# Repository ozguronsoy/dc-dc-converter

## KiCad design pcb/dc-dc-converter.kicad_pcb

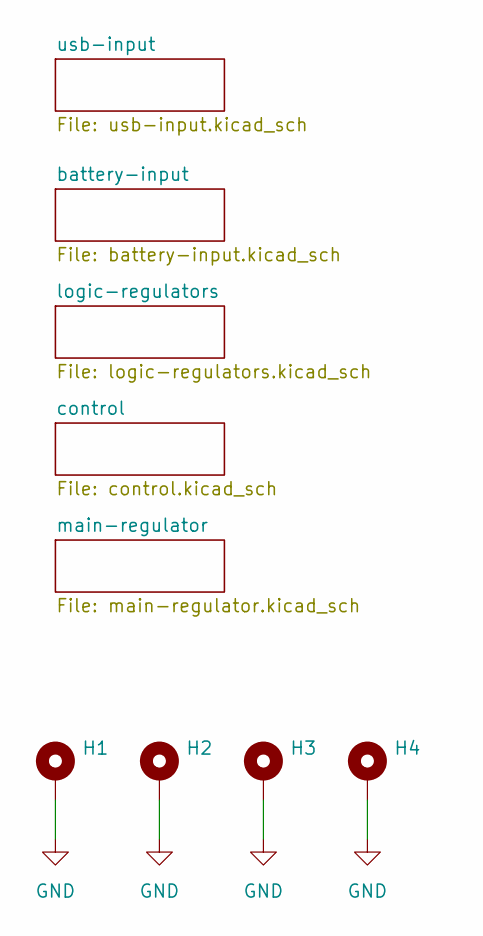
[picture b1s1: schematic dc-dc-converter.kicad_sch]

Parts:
H1, H2, H3, H4: MountingHole_Pad; MountingHole_4.3mm_M4_Pad

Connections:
GND: H1.1, H2.1, H3.1, H4.1; also elsewhere on the board

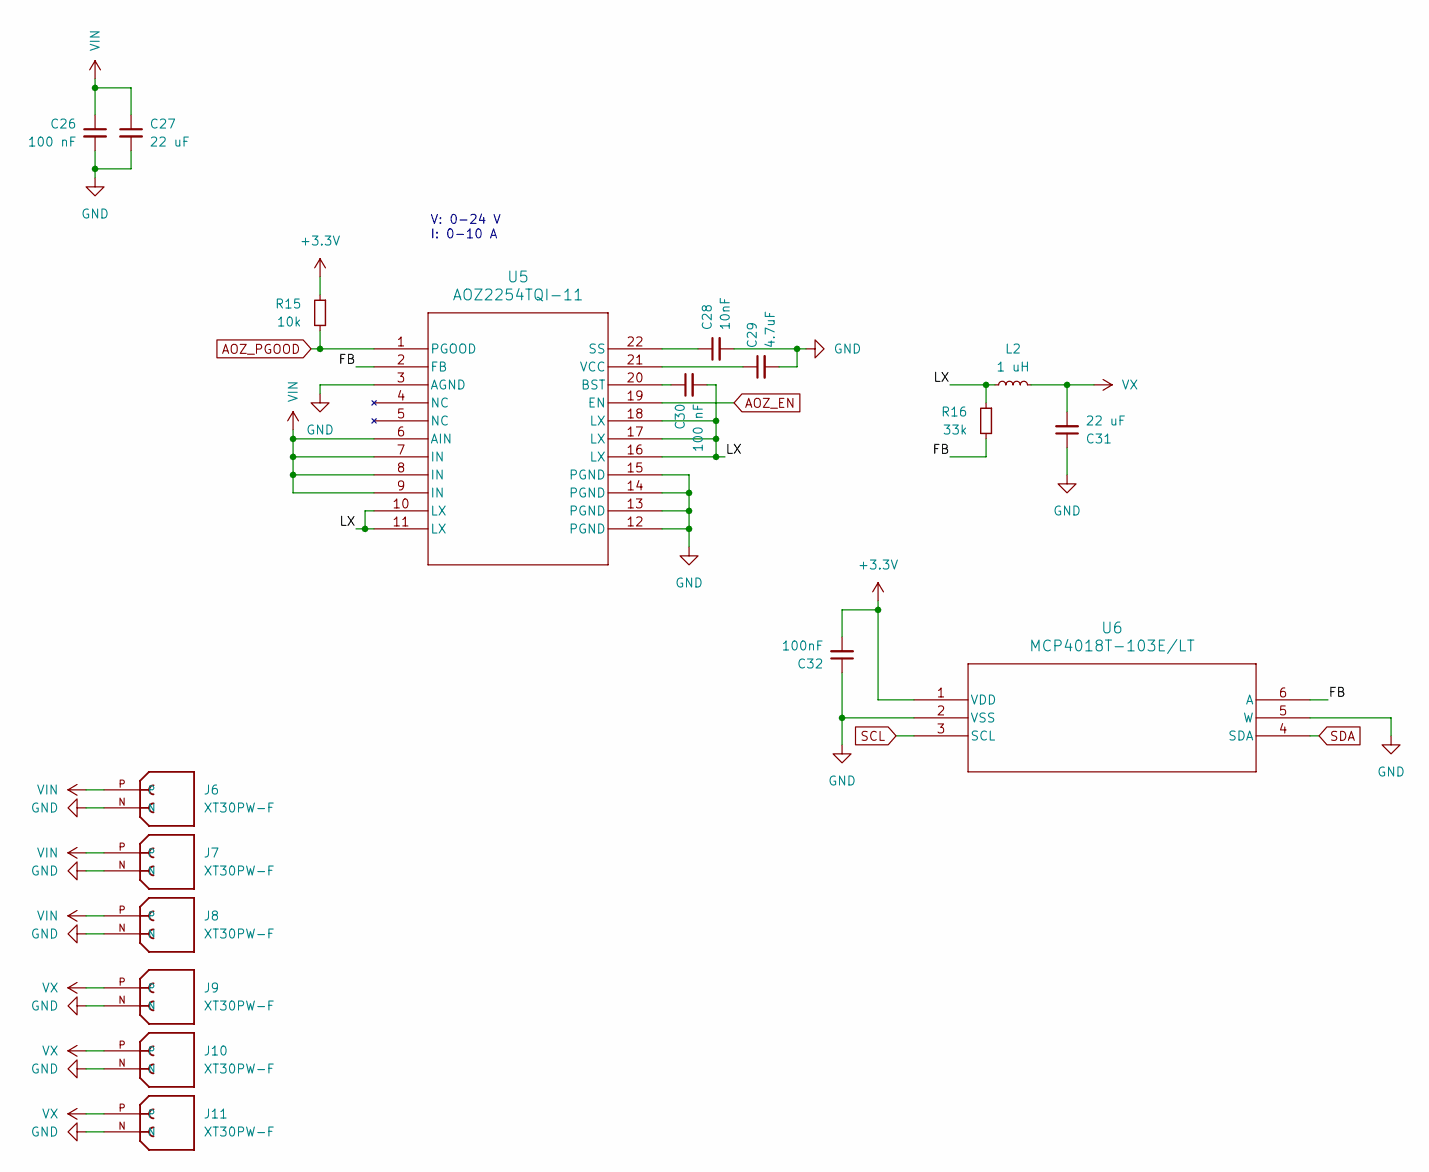
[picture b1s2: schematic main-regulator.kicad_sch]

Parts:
C26: 100 nF; C_0805_2012Metric
C27, C31: 22 uF; C_0805_2012Metric
C28: 10nF; C_0603_1608Metric
C29: 4.7uF; C_0603_1608Metric
C30: 100 nF; C_0603_1608Metric
C32: 100nF; C_0603_1608Metric
J6, J7, J8, J9, J10, J11: XT30PW-F; PARTREV 1.2
L2: 1 uH; L_Chilisin_BMRB00060624
R15: 10k; R_0603_1608Metric
R16: 33k; R_0603_1608Metric
U5: AOZ2254TQI-11
U6: MCP4018T-103E/LT; MCP4018T

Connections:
+3.3V: C32.2, R15.1, U6.1 (VDD); also elsewhere on the board
/main-regulator/FB: R16.2, U5.2 (FB), U6.6 (A)
/main-regulator/LX: C30.2, L2.1, R16.1, U5.10 (LX), U5.11 (LX), U5.16 (LX), U5.17 (LX), U5.18 (LX)
AOZ_EN: U5.19 (EN); also elsewhere on the board
AOZ_PGOOD: R15.2, U5.1 (PGOOD); also elsewhere on the board
GND: C26.2, C27.2, C28.2, C29.2, C31.1, C32.1, J6.N, J7.N, J8.N, J9.N, J10.N, J11.N, U5.3 (AGND), U5.12 (PGND), U5.13 (PGND), U5.14 (PGND), U5.15 (PGND), U6.2 (VSS), U6.5 (W); also elsewhere on the board
unnamed: C30.1, U5.20 (BST)
unnamed: C28.1, U5.22 (SS)
unnamed: C29.1, U5.21 (VCC)
SCL: U6.3 (SCL); also elsewhere on the board
SDA: U6.4 (SDA); also elsewhere on the board
VIN: C26.1, C27.1, J6.P, J7.P, J8.P, U5.6 (AIN), U5.7 (IN), U5.8 (IN), U5.9 (IN); also elsewhere on the board
VX: C31.2, J9.P, J10.P, J11.P, L2.2; also elsewhere on the board

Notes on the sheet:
V: 0-24 V I: 0-10 A

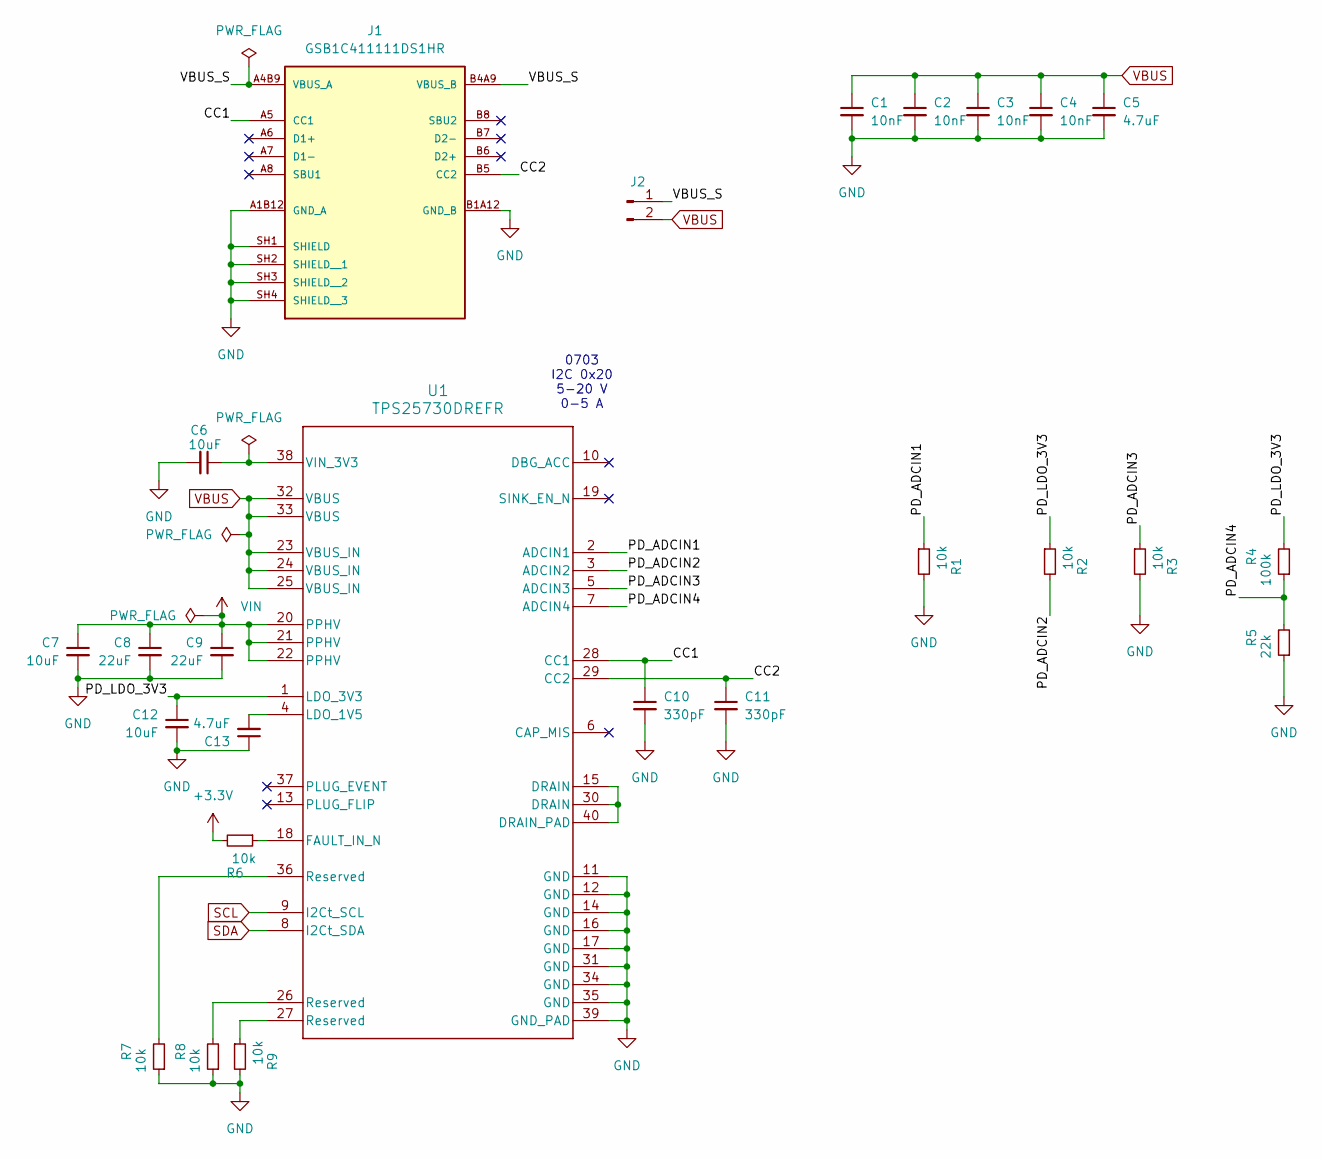
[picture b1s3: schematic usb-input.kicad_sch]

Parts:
C1, C2, C3, C4: 10nF; C_0603_1608Metric
C5, C13: 4.7uF; C_0603_1608Metric
C6, C12: 10uF; C_0603_1608Metric
C7: 10uF; C_0805_2012Metric
C8, C9: 22uF; C_0805_2012Metric
C10, C11: 330pF; C_0402_1005Metric
J1: GSB1C411111DS1HR; PARTREV AX3
J2: Conn_01x02_Pin; PinHeader_1x02_P2.54mm_Vertical
R1, R2, R3, R6, R7, R8, R9: 10k; R_0603_1608Metric
R4: 100k; R_0603_1608Metric
R5: 22k; R_0603_1608Metric
U1: TPS25730DREFR

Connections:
+3.3V: R6.2; also elsewhere on the board
/usb-input/CC1: C10.1, J1.A5 (CC1), U1.28 (CC1)
/usb-input/CC2: C11.1, J1.B5 (CC2), U1.29 (CC2)
/usb-input/PD_ADCIN1: R1.1, U1.2 (ADCIN1)
/usb-input/PD_ADCIN2: R2.2, U1.3 (ADCIN2)
/usb-input/PD_ADCIN3: R3.1, U1.5 (ADCIN3)
/usb-input/PD_ADCIN4: R4.1, R5.2, U1.7 (ADCIN4)
/usb-input/PD_LDO_3V3: C12.1, R2.1, R4.2, U1.1 (LDO_3V3)
/usb-input/VBUS_S: J1.A4B9 (VBUS_A), J1.B4A9 (VBUS_B), J2.1; also elsewhere on the board
GND: C1.2, C2.2, C3.2, C4.2, C5.2, C6.2, C7.2, C8.2, C9.2, C10.2, C11.2, C12.2, C13.1, J1.A1B12 (GND_A), J1.B1A12 (GND_B), J1.SH1 (SHIELD), J1.SH2 (SHIELD__1), J1.SH3 (SHIELD__2), J1.SH4 (SHIELD__3), R1.2, R3.2, R5.1, R7.1, R8.1, R9.2, U1.11 (GND), U1.12 (GND), U1.14 (GND), U1.16 (GND), U1.17 (GND), U1.31 (GND), U1.34 (GND), U1.35 (GND), U1.39 (GND_PAD), U1.44, U1.45, U1.46, U1.47, U1.48; also elsewhere on the board
unnamed: R7.2, U1.36 (Reserved)
unnamed: R8.2, U1.26 (Reserved)
unnamed: R9.1, U1.27 (Reserved)
unnamed: U1.15 (DRAIN), U1.30 (DRAIN), U1.40 (DRAIN_PAD)
unnamed: R6.1, U1.18 (FAULT_IN_N)
unnamed: C13.2, U1.4 (LDO_1V5)
unnamed: C6.1, U1.38 (VIN_3V3)
SCL: U1.9 (I2Ct_SCL); also elsewhere on the board
SDA: U1.8 (I2Ct_SDA); also elsewhere on the board
VBUS: C1.1, C2.1, C3.1, C4.1, C5.1, J2.2, U1.23 (VBUS_IN), U1.24 (VBUS_IN), U1.25 (VBUS_IN), U1.32 (VBUS), U1.33 (VBUS); also elsewhere on the board
VIN: C7.1, C8.1, C9.1, U1.20 (PPHV), U1.21 (PPHV), U1.22 (PPHV); also elsewhere on the board

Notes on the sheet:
0703 I2C 0x20 5-20 V 0-5 A

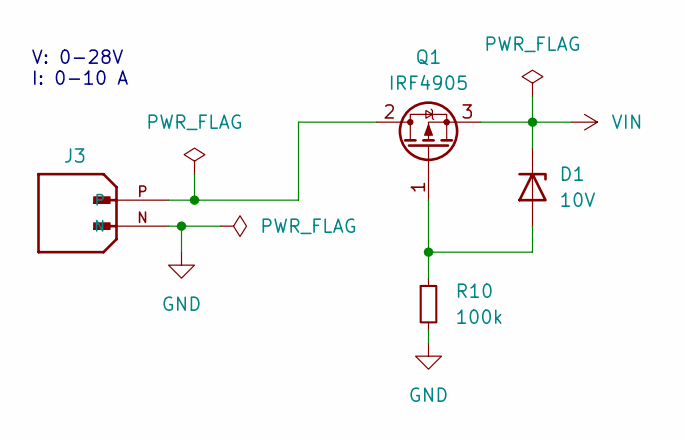
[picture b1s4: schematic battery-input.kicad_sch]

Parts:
D1: 10V; D_SOD-523
J3: XT30PW-M; PARTREV 1.2
Q1: IRF4905; TO-220-3_Vertical
R10: 100k; R_0603_1608Metric

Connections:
GND: J3.N, R10.2; also elsewhere on the board
unnamed: D1.2 (A), Q1.1 (G), R10.1
unnamed: J3.P, Q1.2 (D)
VIN: D1.1 (K), Q1.3 (S); also elsewhere on the board

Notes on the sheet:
V: 0-28V I: 0-10 A

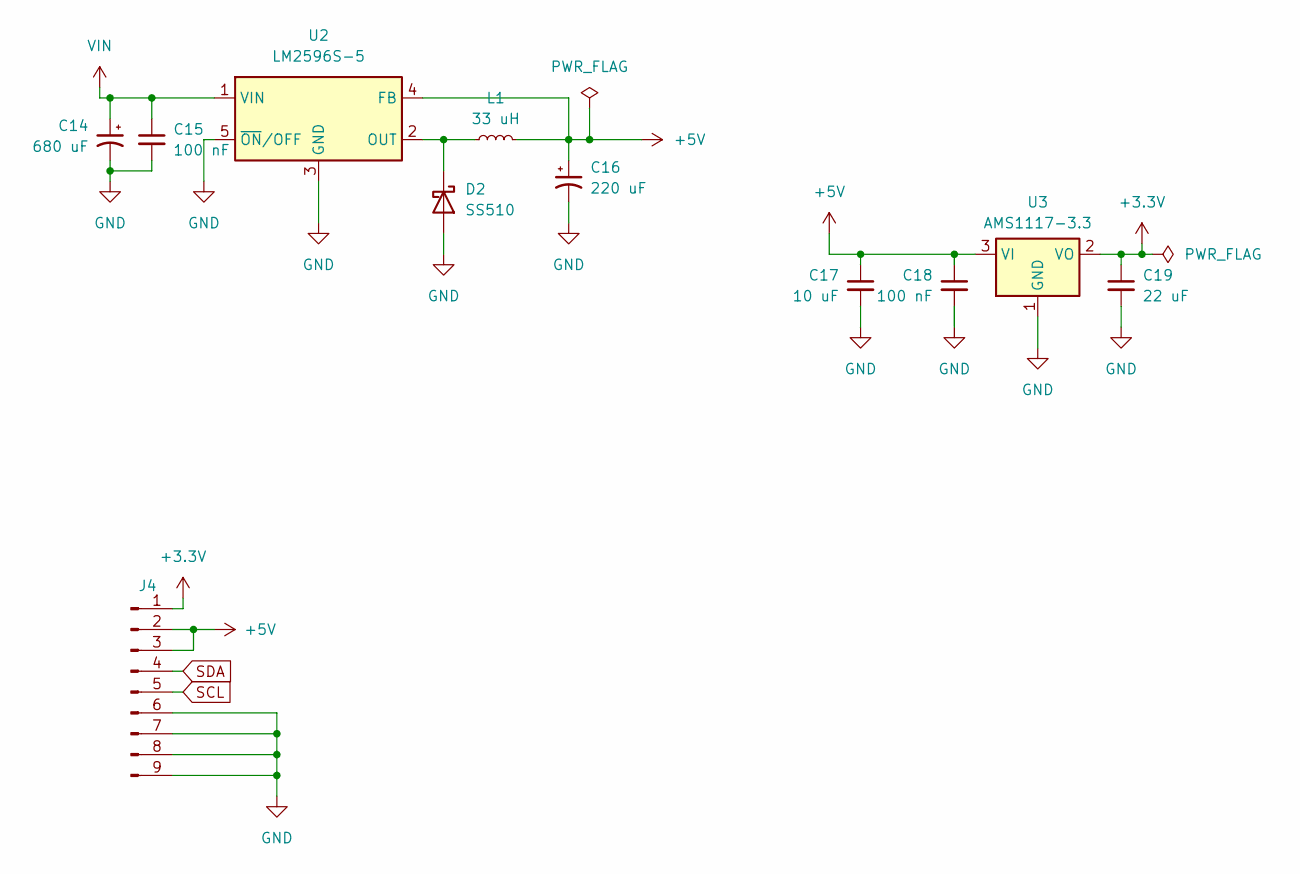
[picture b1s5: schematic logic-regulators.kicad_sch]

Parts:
C14: 680 uF; C_Radial_D12.5mm_H20.0mm_P5.00mm
C15: 100 nF; C_0805_2012Metric
C16: 220 uF; C_Radial_D12.5mm_H20.0mm_P5.00mm
C17: 10 uF; C_0603_1608Metric
C18: 100 nF; C_0603_1608Metric
C19: 22 uF; C_0603_1608Metric
D2: SS510; D_SMA
J4: JST_EH_B9B-EH-A_1x09_P2.50mm_Vertical
L1: 33 uH; L_SXN_SMDRI127
U2: LM2596S-5; TO-263-5_TabPin3
U3: AMS1117-3.3; SOT-223-3_TabPin2

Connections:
+3.3V: C19.1, J4.1, U3.2 (VO); also elsewhere on the board
+5V: C16.1, C17.1, C18.1, J4.2, J4.3, L1.2, U2.4 (FB), U3.3 (VI); also elsewhere on the board
GND: C14.2, C15.2, C16.2, C17.2, C18.2, C19.2, D2.2 (A), J4.6, J4.7, J4.8, J4.9, U2.3 (GND), U2.5 (~ON/OFF), U3.1 (GND); also elsewhere on the board
unnamed: D2.1 (K), L1.1, U2.2 (OUT)
SCL: J4.5; also elsewhere on the board
SDA: J4.4; also elsewhere on the board
VIN: C14.1, C15.1, U2.1 (VIN); also elsewhere on the board

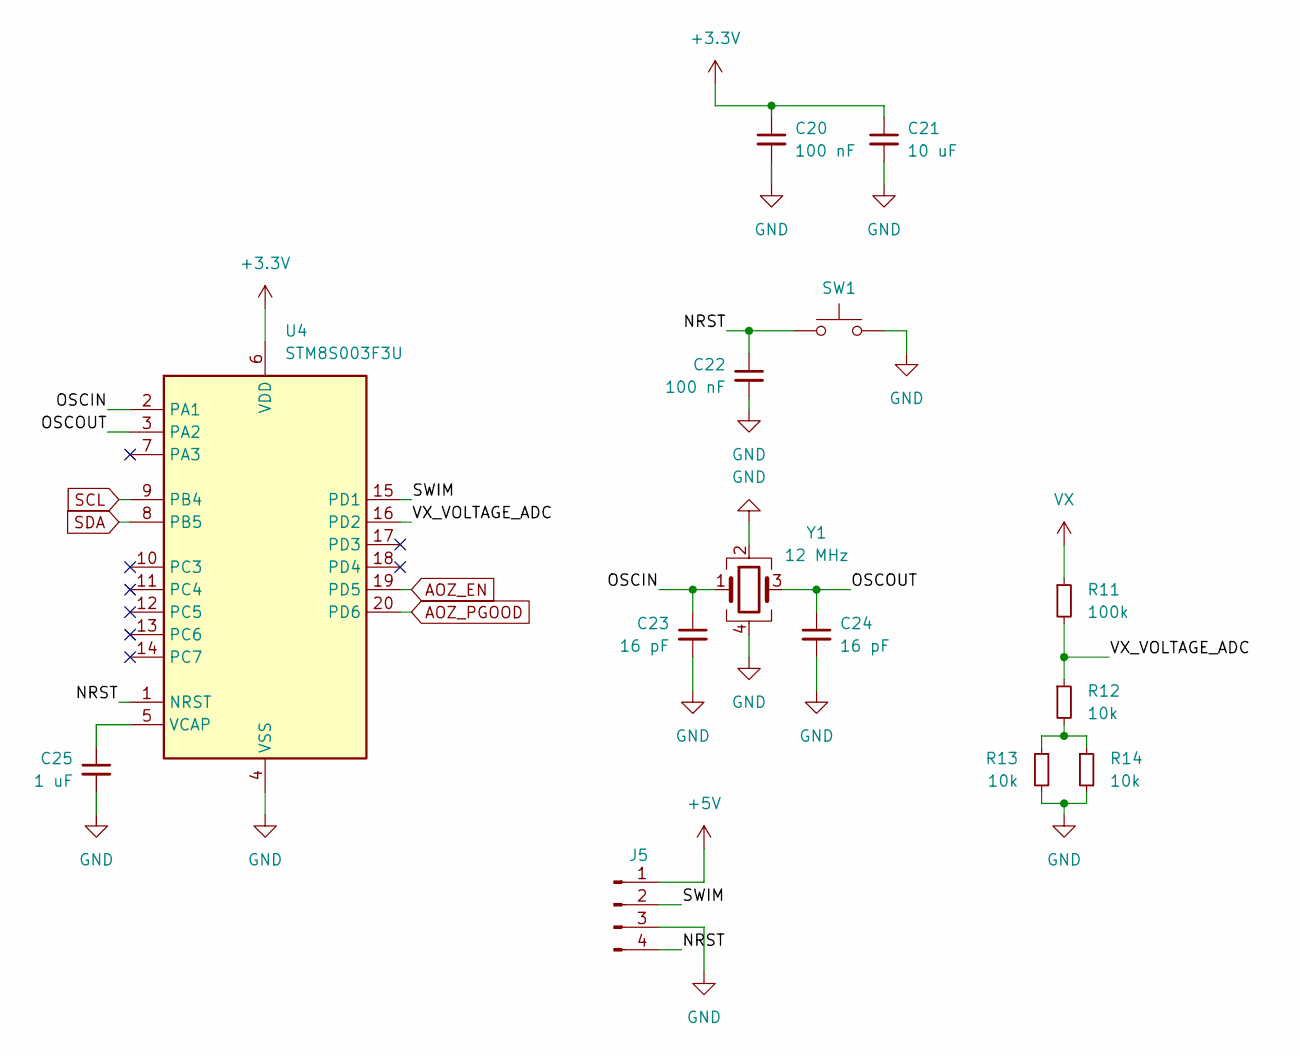
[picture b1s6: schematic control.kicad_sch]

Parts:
C20, C22: 100 nF; C_0603_1608Metric
C21: 10 uF; C_0603_1608Metric
C23, C24: 16 pF; C_0402_1005Metric
C25: 1 uF; C_0603_1608Metric
J5: Conn_01x04_Pin; PinHeader_1x04_P2.54mm_Vertical
R11: 100k; R_0603_1608Metric
R12, R13, R14: 10k; R_0603_1608Metric
SW1: SW_Push; SW_Tactile_SPST_NO_Straight_CK_PTS636Sx25SMTRLFS
U4: STM8S003F3U; ST_UFQFPN-20_3x3mm_P0.5mm
Y1: 12 MHz; Crystal_SMD_3225-4Pin_3.2x2.5mm

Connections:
+3.3V: C20.1, C21.1, U4.6 (VDD); also elsewhere on the board
+5V: J5.1; also elsewhere on the board
/control/NRST: C22.1, J5.4, SW1.1, U4.1 (NRST)
/control/OSCIN: C23.1, U4.2 (PA1), Y1.1
/control/OSCOUT: C24.1, U4.3 (PA2), Y1.3
/control/SWIM: J5.2, U4.15 (PD1)
/control/VX_VOLTAGE_ADC: R11.2, R12.1, U4.16 (PD2)
AOZ_EN: U4.19 (PD5); also elsewhere on the board
AOZ_PGOOD: U4.20 (PD6); also elsewhere on the board
GND: C20.2, C21.2, C22.2, C23.2, C24.2, C25.2, J5.3, R13.2, R14.2, SW1.2, U4.4 (VSS), Y1.2, Y1.4; also elsewhere on the board
unnamed: R12.2, R13.1, R14.1
unnamed: C25.1, U4.5 (VCAP)
SCL: U4.9 (PB4); also elsewhere on the board
SDA: U4.8 (PB5); also elsewhere on the board
VX: R11.1; also elsewhere on the board

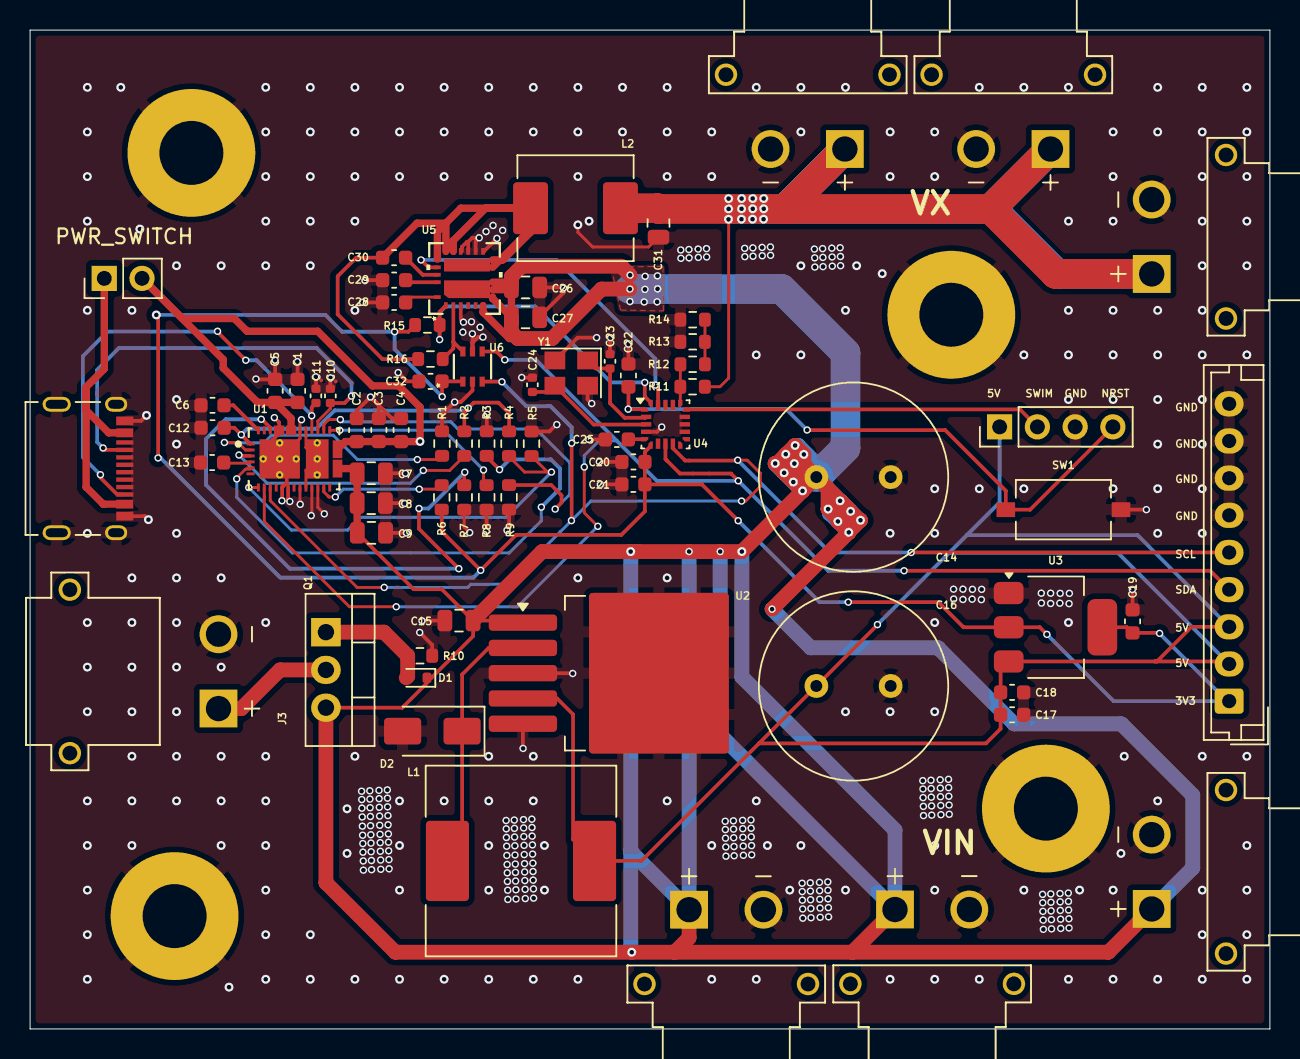
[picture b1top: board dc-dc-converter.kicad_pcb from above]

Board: 2 copper layers, 83.4 x 67.2 mm, 76 parts (0 on the bottom side), 40 nets.

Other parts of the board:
PWR_SWITCH: Conn_01x02_Pin; PinHeader_1x02_P2.54mm_Vertical

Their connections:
/usb-input/VBUS_S: PWR_SWITCH.1; also elsewhere on the board
VBUS: PWR_SWITCH.2; also elsewhere on the board

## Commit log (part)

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2025-10-26 impl batt input & logic regulators
2025-10-27 drawn control schematics
2025-10-27 added pull-up to i2c
2025-10-28 drawn usb input schematics
2025-10-30 finished drawing schematics
2025-10-30 finished component placements
2025-11-17 drawn pcb paths
2025-11-17 add mounting holes
2025-11-21 remove i2c pull-ups & add switch to usb-c power input
2025-11-27 create code, impl clock selection & adc conversion
